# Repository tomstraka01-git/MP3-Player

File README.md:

# MP3-Player

## What is it?
MP3-Player is a DYI project made by me. It can:
- Play songs from a microSD card directly to your earphones.
- Stay on battery for multiple hours.
- Show you info about battery charge and info about song (time, song name, playing/not playing, etc.).
- Be controlled with 5 buttons.

## Why?
I like listening to music and making my own hardware/software projects, and i also wanted to learn more about how these things are made, so i chose to make one myself. 

## How to use?
1. Solder all the components to the custom PCB board.
2. 3D print the case and the battery hatch.
3. Screw the PCB securely into the case.
4. Download the firmware and flash it using the Arduino IDE.
5. Format a microSD card, add your `.mp3` or `.wav` songs directly to the root directory, and plug it into the reader.
6. Connect your charged Li-Po battery and you can now listen to your songs.

## Software
I wrote the main firmware in arduino ide c++. To flash the board, you must install arduino ide and the libraries i am using. Then connect the micro usb cable to the mcu, and flash the code. The code handles all the communications between the modules, plays the song to the PCM5102A and creates the ui, checks for buttons, checks battery etc.

## Electronics

I used a custom PCB, which takes power from a 3.7 Li-Po 450 mah (the battery should last for few hours) and passes it through a fast fuse for short circuit protection and diode for reverse connection protection. Then it goes to the rasberry pi pico 2 WH, which converts the power to stable 3.3V. The MCU reads the micro sd card reader module through spi, and then plays the song into the PCM5102A. It also displays all the info to the oled screen, and checks the five buttons for input. The five buttons have these features:
- Volume Down
- Volume Up
- Previous Song
- Next Song
- Play/Pause

## Features
- ### Has a 3.5mm audio jack output, you can connect your earphones to it and listen directly.

- ### Has a micro SD card reader, put the micro SD card inside and listen to your songs.

- ### Has a micro USB port, so you can flash your own firmware or debug software issues.

# Bill of Materials (BOM)

| Item Name | Qty | Price (total) (USD) | Item Link | Notes |
|---|---|---|---|---|
| Resistor 10k | 5 | $0.24 | [Link](https://dratek.cz/arduino-platforma/7650-rezistor-10k-0.25-w-1.html) | Resistors for buttons, so that the circuit works |
| Button | 5 | $0.47 | [Link](https://dratek.cz/arduino-platforma/176310-mikrospinac-tlacitko-6-x-6-x-8-mm.html) | The buttons, used for skipping songs, changing volume, pausing, etc. |
| GY-PCM5102 I2S audio module | 1 | $4.61 | [Link](https://www.laskakit.cz/gy-pcm5102-i2s-audio-modul/) | The audio generator, changes digital sound to analog |
| 3.3V micro SD card module | 1 | $3.20 | [Link](https://www.laskakit.cz/laskakit-microsd-card-modul/) | Micro SD card reader, reads the micro SD card |
| OLED display 128x64 white | 1 | $7.86 | [Link](https://dratek.cz/arduino-platforma/3181-iic-i2c-oled-1-3-displej-128x64-bily.html) | OLED display, shows the user data like volume, info about songs, battery percent etc. |
| Resistor 100k | 1 | $0.05 | [Link](https://dratek.cz/arduino-platforma/7653-rezistor-100k-0.25-w-1.html) | Resistor for voltage divider, which steps down the voltage so the ADC can read it |
| Resistor 330k | 1 | $0.05 | [Link](https://dratek.cz/arduino-platforma/174965-metalizovany-rezistor-330k-0-25w-1.html) | Resistor for voltage divider, which steps down the voltage so the ADC can read it |
| Condensator 100µF 50V | 4 | $0.20 | [Link](https://dratek.cz/arduino-platforma/7825-kondenzator-100uf-50v.html) | Condensators, smooths the voltage and evens out current spikes |
| Fuse Fast 250V 2A | 10 | $0.19 | [Link](https://www.tme.eu/cz/details/zks-2a/pojistky-5x20mm-rychle/eska/520-620/) | Fast fuses — if there is a short circuit, the fuses blow and disconnect the battery from the circuit, protecting the battery and the person |
| Diode Schottky; THT; 40V; 3A; DO201AD; Ufmax: 0.475V | 2 | $0.64 | [Link](https://www.tme.eu/cz/details/1n5822-st/diody-schottky-tht/stmicroelectronics/1n5822/) | Diode, prevents opposite polarity battery connections |
| Dupont female pins | 1 | $0.33 | [Link](https://dratek.cz/arduino-platforma/913-dupont-dutinkova-lista-samice-samec.html?cv) | Used for plugging in the OLED display and other things |
| Dupont male pins | 1 | $0.15 | [Link](https://dratek.cz/arduino-platforma/1331-dupont-40pin-2-54-mm-kolikova-lista-rovna.html) | Same as above, but male version |
| JST 6-pin connector | 2 | $1.49 | [Link](https://www.tme.eu/cz/katalog/signalove-konektory-raster-1-00mm_112946/?queryPhrase=SM06B&keywordSetName=extended) | SMD JST 6-pin connector, connects the micro SD card reader to the main PCB |
| JST 6-pin cable | 2 | $1.41 | [Link](https://dratek.cz/arduino-platforma/122186-jst-sh-1.0mm-6-pin-vodic-samice.html) | The cable for the SMD JST connector |
| Schurter fuse holder 10A 20x5mm | 2 | $2.28 | [Link](https://www.tme.eu/cz/details/0031.8211/pojistkova-pouzdra-do-pcb/schurter/) | Fuse holder — holds the fuse so it can be replaced when blown, no desoldering needed |
| JST battery terminal | 3 | $0.93 | [Link](https://www.tme.eu/cz/details/s2b-ph-k-s/signalove-konektory-raster-2-00mm/jst/s2b-ph-k-s-lf-sn/) | Battery terminal — the battery connects to it and distributes the power |
| Raspberry Pi Pico 2 WH | 1 | $9.71 | [Link](https://www.tme.eu/cz/details/sc1634/raspberry-pi-vestavene-systemy/raspberry-pi/raspberry-pi-pico-2-wh/) | The main brain of the system — reads the micro SD card, runs the UI menu, sends the sound output to the sound chip |
| Li-Po battery 3.7V 450mAh | 1 | $5.90 | [Link](https://dratek.cz/arduino-platforma/179445-lipol-baterie-502248-450mah-3-7v.html) | Shipping to Czech Republic |
| JLCPCB PCB | 5 | $3.20 | [Link](https://cart.jlcpcb.com/quote?stencilLayer=2&stencilWidth=100&stencilLength=100&stencilCounts=5&plateType=1&spm=Jlcpcb.Homepage.1010) | Shipping to Czech Republic |
| Shipping — Dratek.cz | 1 | $4.00 | [Link](https://www.dratek.cz) | Shipping to Czech Republic |
| Shipping — TME.eu | 1 | $8.47 | [Link](https://www.tme.eu/) | |
| Shipping — LaskaKit | 1 | $3.76 | [Link](https://www.laskakit.cz) | |
| Shipping — JLCPCB | 1 | $12.00 | [Link](https://jlcpcb.com/) | |
| **Total Price (USD)** | | **$65.82** | | |

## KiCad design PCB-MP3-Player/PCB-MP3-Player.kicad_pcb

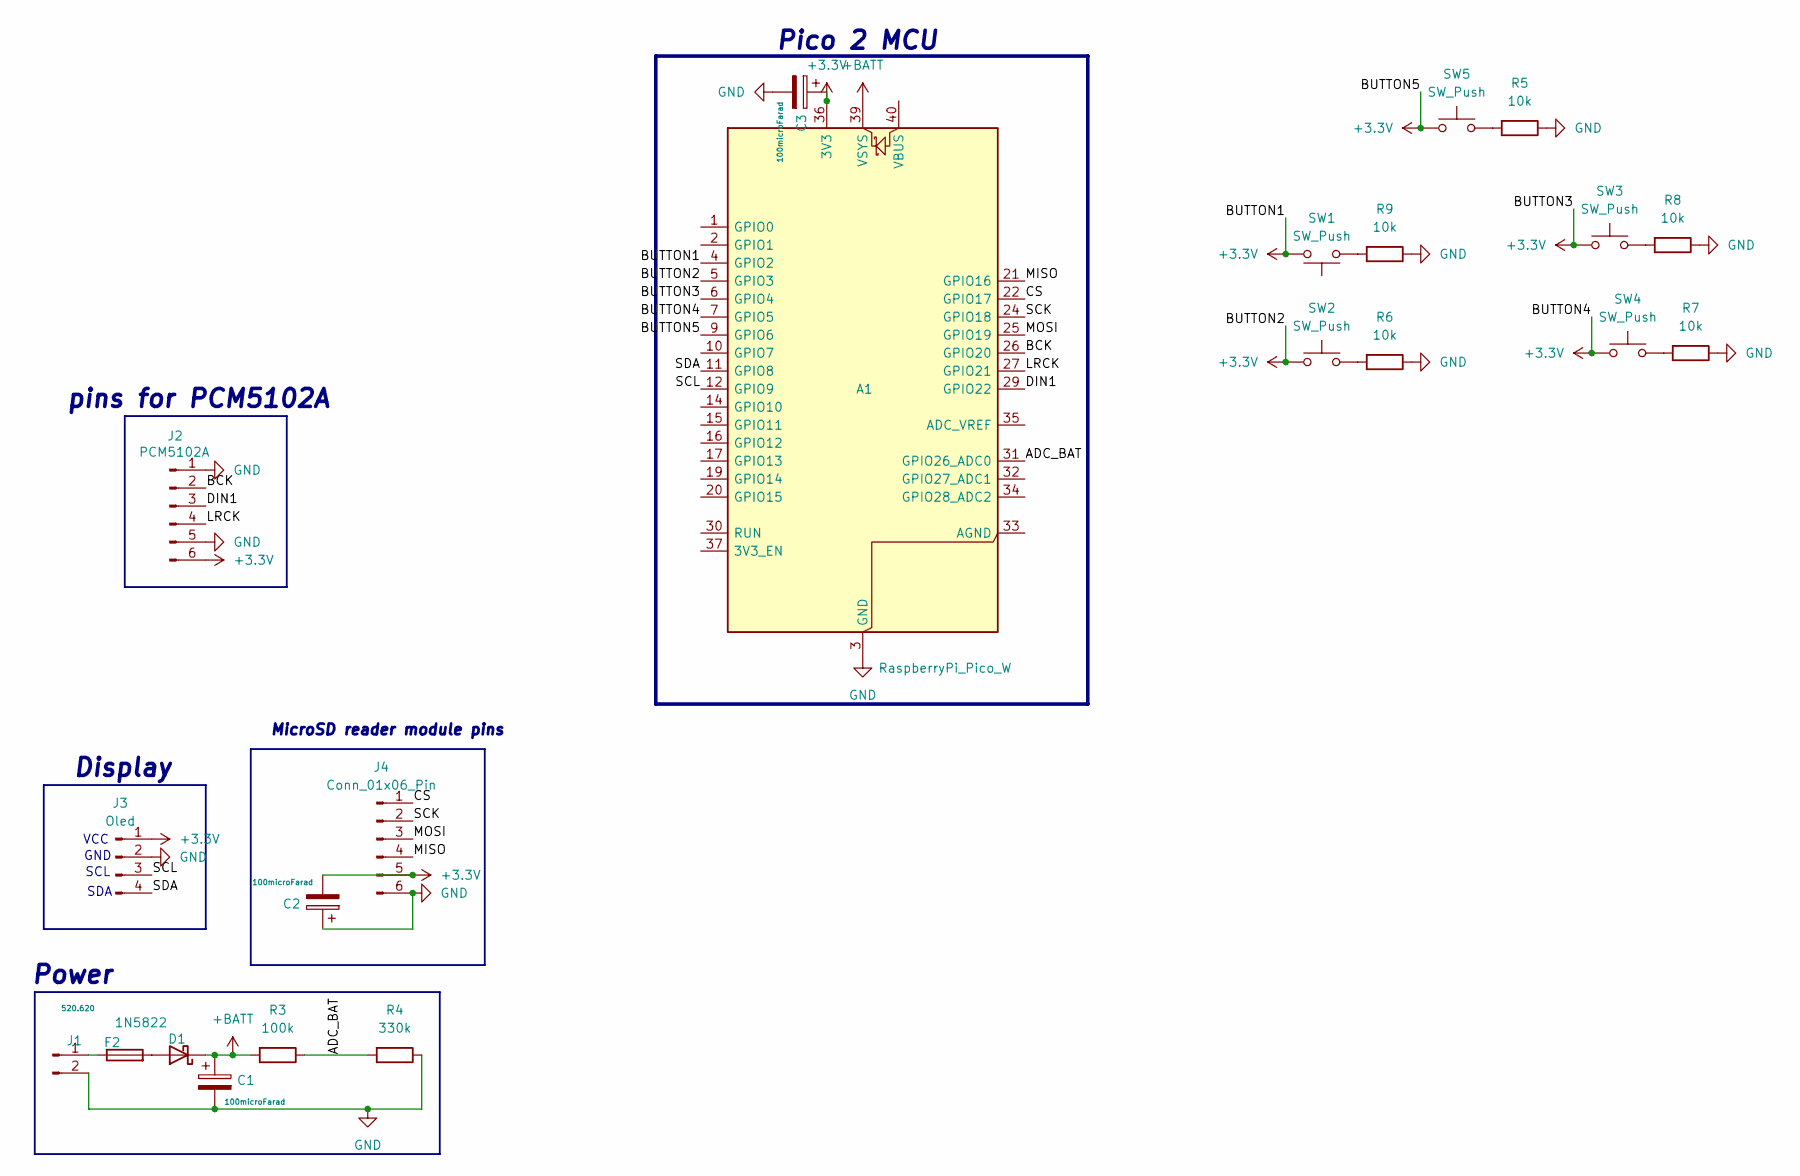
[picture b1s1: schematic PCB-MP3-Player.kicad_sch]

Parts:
A1: RaspberryPi_Pico_W; RaspberryPi_Pico_Common_THT
C1, C2, C3: 100microFarad; CP_Radial_D6.3mm_P2.50mm
D1: 1N5822; D_DO-201AD_P15.24mm_Horizontal
F2: 520.620; Fuseholder_Cylinder-5x20mm_Schurter_0031_8201_Horizontal_Op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
J1: Conn_01x02_Pin; JST_PH_S2B-PH-K_1x02_P2.00mm_Horizontal
J2: PCM5102A; PinSocket_1x06_P2.54mm_Vertical
J3: Oled; PinSocket_1x04_P2.54mm_Vertical
J4: Conn_01x06_Pin; JST_SH_SM06B-SRSS-TB_1x06-1MP_P1.00mm_Horizontal
R3: 100k; R_Axial_DIN0207_L6.3mm_D2.5mm_P7.62mm_Horizontal
R4: 330k; R_Axial_DIN0207_L6.3mm_D2.5mm_P7.62mm_Horizontal
R5, R6, R7, R8, R9: 10k; R_Axial_DIN0207_L6.3mm_D2.5mm_P7.62mm_Horizontal
SW1, SW2, SW3, SW4, SW5: SW_Push; SW_PUSH_6mm_H4.3mm

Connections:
+3.3V: A1.4 (GPIO2), A1.5 (GPIO3), A1.6 (GPIO4), A1.7 (GPIO5), A1.9 (GPIO6), A1.36 (3V3), C2.2, C3.1, J2.6, J3.1, J4.5, SW1.2, SW2.1, SW3.1, SW4.1, SW5.1
+BATT: A1.39 (VSYS), C1.1, D1.1 (K), R3.2
/ADC_BAT: A1.31 (GPIO26_ADC0), R3.1, R4.2
/BCK: A1.26 (GPIO20), J2.2
/CS: A1.22 (GPIO17), J4.1
/DIN1: A1.29 (GPIO22), J2.3
/LRCK: A1.27 (GPIO21), J2.4
/MISO: A1.21 (GPIO16), J4.4
/MOSI: A1.25 (GPIO19), J4.3
/SCK: A1.24 (GPIO18), J4.2
/SCL: A1.12 (GPIO9), J3.3
/SDA: A1.11 (GPIO8), J3.4
GND: A1.3 (GND), A1.8 (GND), A1.13 (GND), A1.18 (GND), A1.23 (GND), A1.28 (GND), A1.38 (GND), C1.2, C2.1, C3.2, J1.2, J2.1, J2.5, J3.2, J4.6, R4.1, R5.1, R6.1, R7.1, R8.1, R9.1
unnamed: D1.2 (A), F2.2
unnamed: F2.1, J1.1
unnamed: R5.2, SW5.2
unnamed: R6.2, SW2.2
unnamed: R7.2, SW4.2
unnamed: R8.2, SW3.2
unnamed: R9.2, SW1.1

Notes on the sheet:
SCL
Display
Pico 2 MCU
pins for PCM5102A
VCC
GND
MicroSD reader module pins
Power
SDA

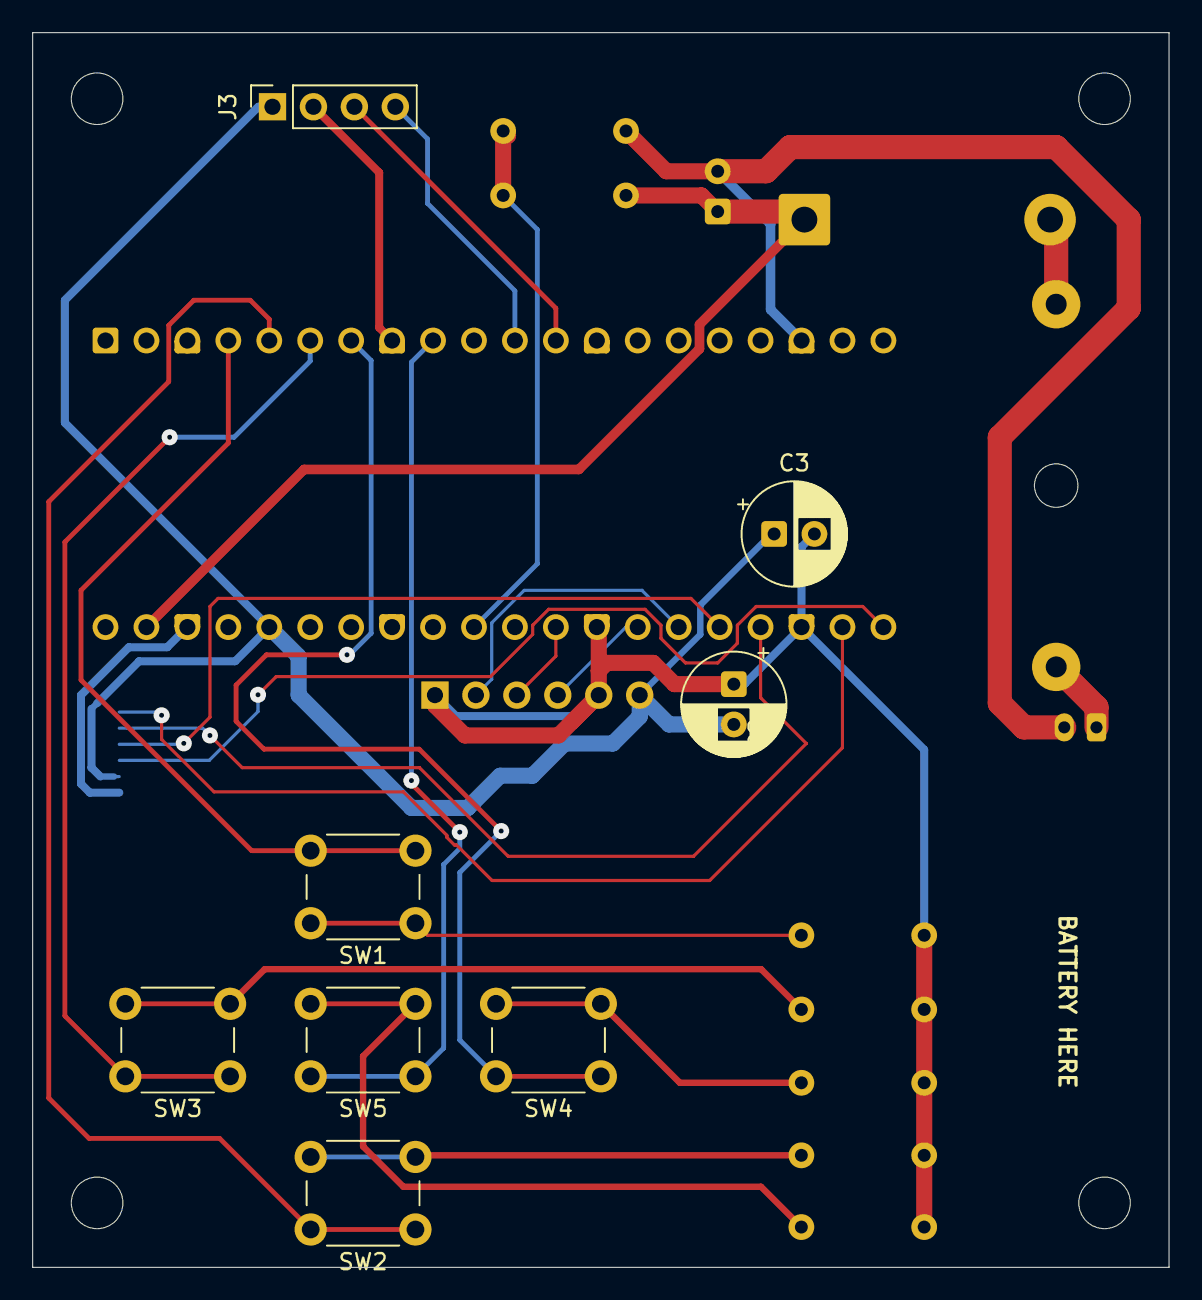
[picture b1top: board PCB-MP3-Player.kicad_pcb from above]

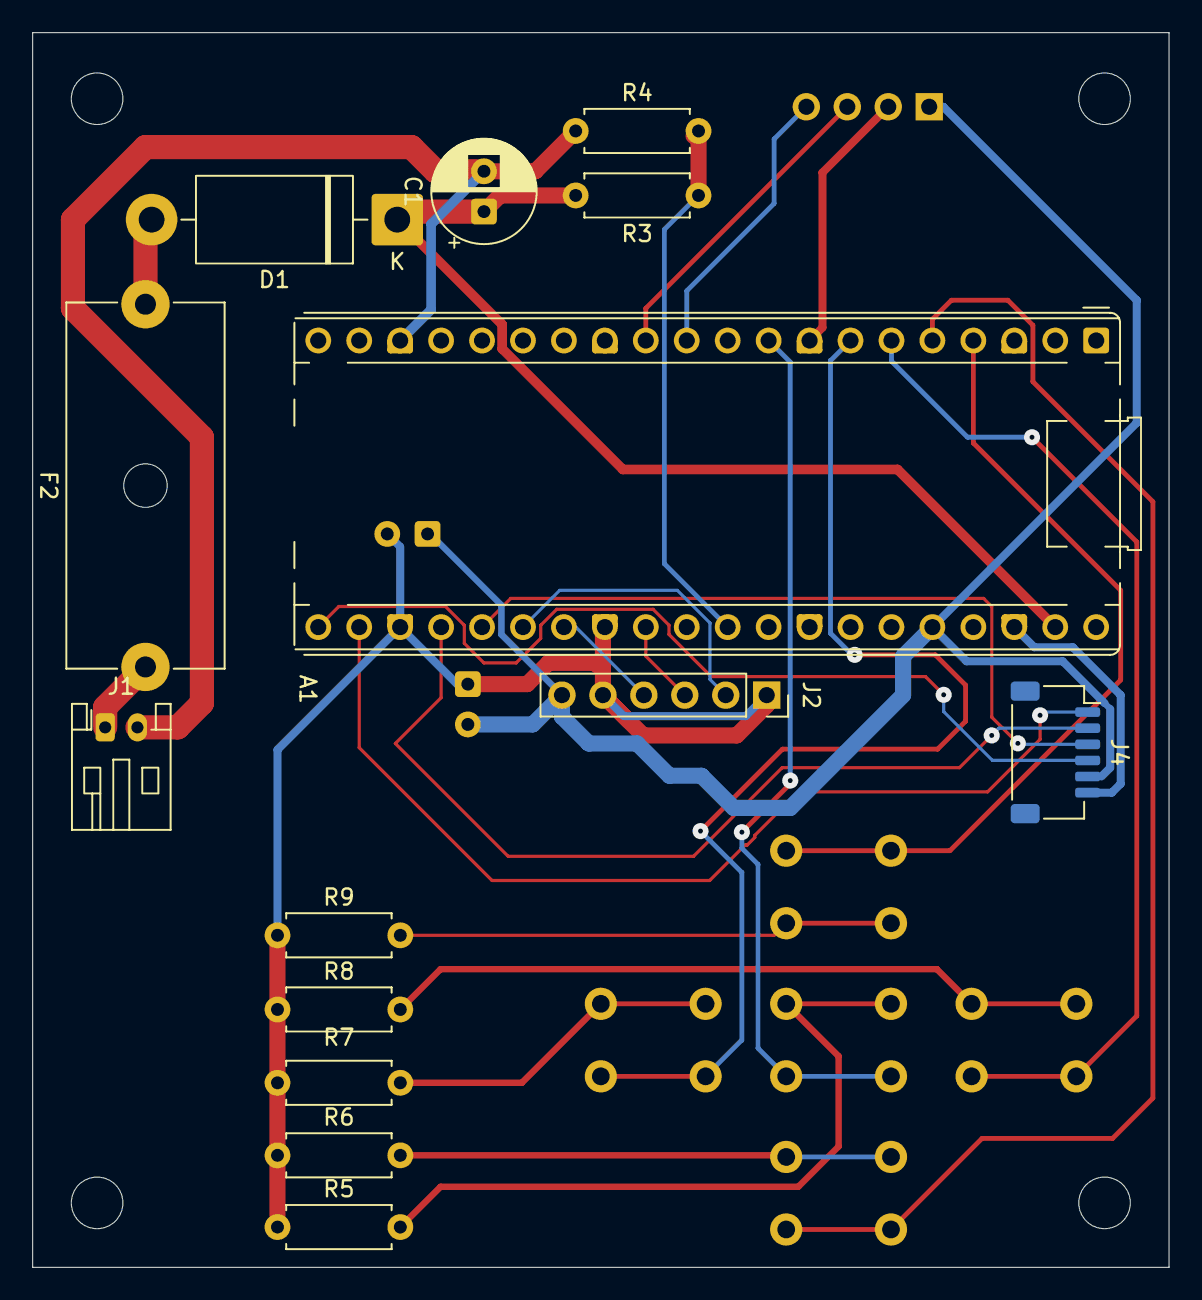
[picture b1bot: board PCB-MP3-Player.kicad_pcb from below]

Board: 2 copper layers, 70.5 x 76.6 mm, 22 parts (14 on the bottom side), 20 nets.

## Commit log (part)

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2026-06-20 first commit, added some components to the pcb. Started thinking about the project
2026-06-22 connected components together
2026-06-22 first code commit
